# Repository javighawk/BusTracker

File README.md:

# BusTracker
Bus tracker in Raspberry Pi originally designed for Saskatoon transit. It will check the waiting time on desired stop(s) and display it on a 7-segment display.

Dependencies arre mantained through Ivy

The material used is:
- Raspberry Pi 3
- Adafruit 1.2" 7-segment red
- 2x Buttons

To run the program:
1. Place the GTFS static data on the folder "gtfs/" located on the base directory of the repository.
2. Run  Main.java. You will probably need to run it as superuser.

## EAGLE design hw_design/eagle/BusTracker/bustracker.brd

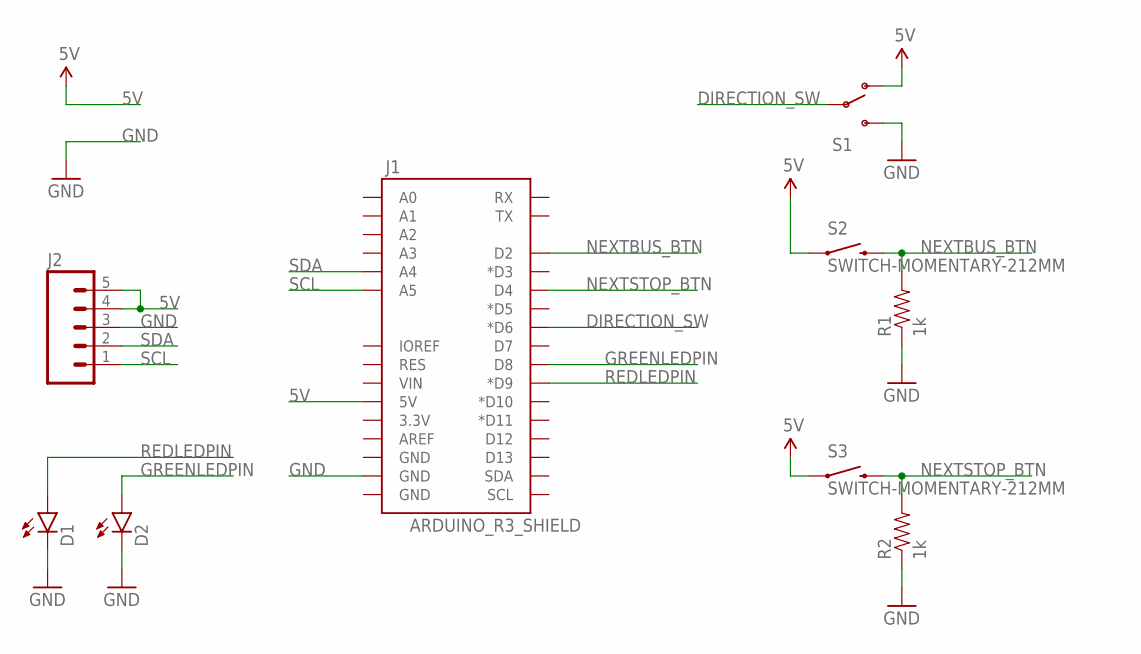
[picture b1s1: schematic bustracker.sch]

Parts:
D1, D2: LED5MM
J1: ARDUINO_R3_SHIELD; UNO_R3_SHIELD
J2: M05PTH; 1X05
R1, R2: 1k; AXIAL-0.3
S1: SWITCH-SPDTPTH; SWITCH-SPDT
S2, S3: SWITCH-MOMENTARY-212MM; TACTILE-PTH-12MM

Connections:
5V: J1.5V, J2.4, J2.5, S1.1 (O), S2.1, S3.1
DIRECTION_SW: J1.D6 (*D6), S1.2
GND: D1.K (C), D2.K (C), J1.GND@1 (GND), J2.3, R1.P$1 (1), R2.P$1 (1), S1.3 (S)
GREENLEDPIN: D2.A, J1.D8
NEXTBUS_BTN: J1.D2, R1.P$2 (2), S2.3 (2)
NEXTSTOP_BTN: J1.D4, R2.P$2 (2), S3.3 (2)
REDLEDPIN: D1.A, J1.D9 (*D9)
SCL: J1.A5, J2.1
SDA: J1.A4, J2.2

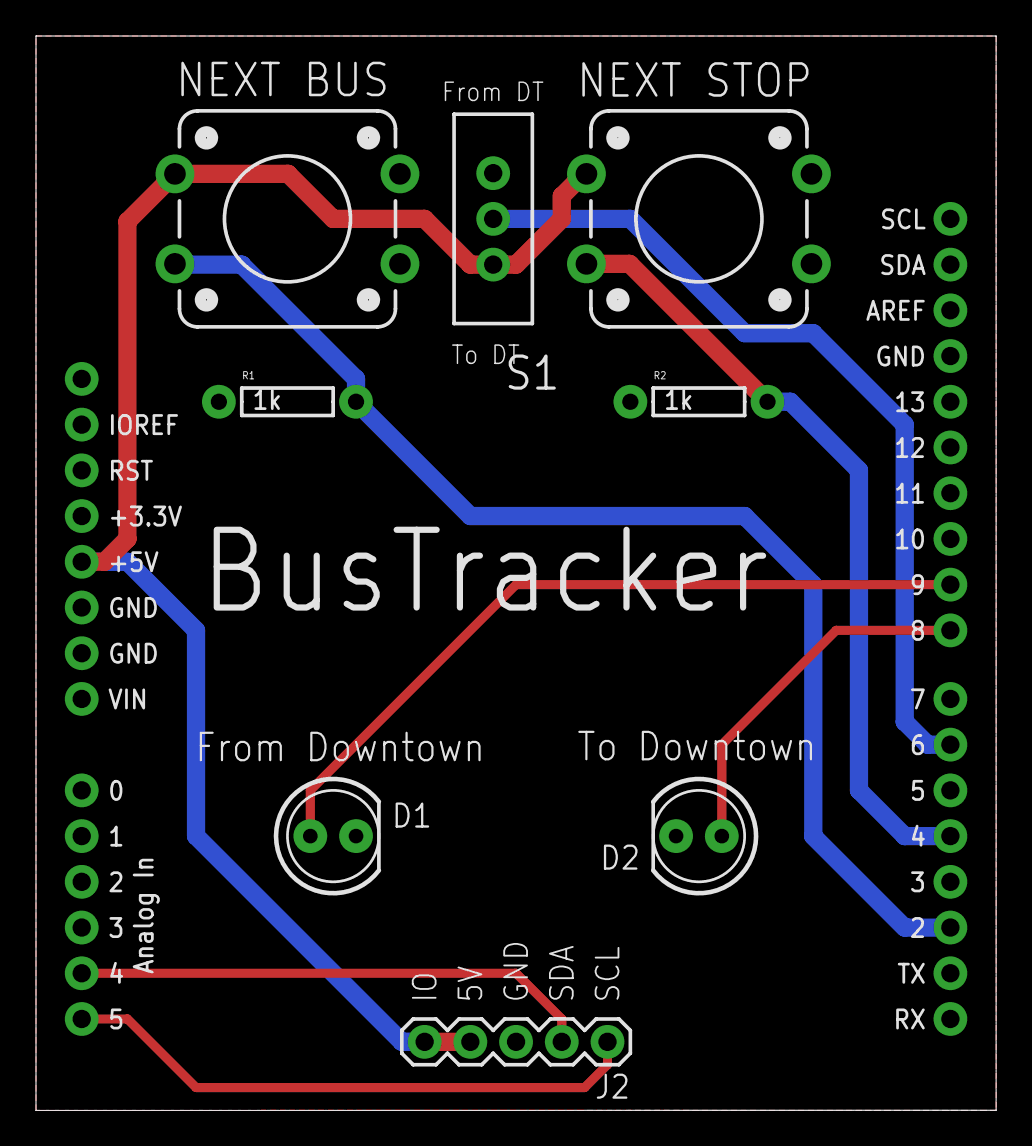
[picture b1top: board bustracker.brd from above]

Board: 2 copper layers, 53.3 x 59.7 mm, 9 parts (0 on the bottom side), 9 nets.

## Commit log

2016-01-27 :circus_tent: Added .gitattributes & .gitignore files
2016-01-27 Initial commit
    All files added
2016-01-31 Added waiting time calculation
    Added waiting time calculation.
    Erased the scheduled times from the program. They need to be taken from
    the GTFS feed and stored until they are outdated.
    Added 3 more bus stops but not being used at the moment
2016-02-05 Ported to Arduino
    All the program done in Eclipse has been ported to Arduino since the
    libraries to use the 7-segment display are for Arduino
2016-02-05 Added readme
2016-02-06 Added bus line parsing and error displaying
    Bus lines are now also parsed.
    Errors during the website download are displayed now in the 7-segment
    displayed
2016-02-12 Included lastTime variable
    Included a variable to show when was the last time the BusStop data was
    updated
2016-02-12 Fixed bus line display
    Fixed the displaying of the bus line. Now the bus line is always
    displayed either there is wait time information or not.
    Changed the error display format: Connection error will be shown now
    with a small dot over the waiting time and a not updated wait time will
    be signaled with the semicolon between the line and the wait time.
2016-02-12 Fixed connection problems handling
    Modified the way the connection problems are handled, so at no moment
    the program should get stuck, but notify the problem through the display
2016-02-12 Fixed a bug in time at noon & lastUpdated refresh
    Fixed a bug that appeared when it was 12PM, where the waiting time
    suddenly appeared to be 12 hours of wait.
    Added also a line to update the lastUpdated variable of the BusStop that
    we are parsing for.
2016-02-12 Added interrupts for GPIO and a function to retrieve all the info
    Added interrupts to handle two buttons to show different wait times and
    bus lines.
    Added a function that retrieves the informaton given a set of bus stops
2016-04-09 Added some comments
2016-07-23 Reviewed code for Arduino
2016-07-23 Added info to some comments
2016-07-23 Fixed indentation
2016-07-23 Modified comments and bus stop name. Added watchdog func
2016-07-23 Modified comments and removed unused functions
2016-07-23 Modif comments, added display funcs, removd unused vars
2016-07-23 Modified comments
2016-07-23 Revert "Finished Watchdog implementation"
2016-07-23 Added comments
2016-07-24 Removed interrupts due to malfunction
2016-07-24 Stored strings in defines
2016-07-24 Erased colon switch
2016-07-24 Added new bus line
2016-07-24 Changed analogRead for Interrupt. Added intrrpt unbouncing function
2016-07-24 Arranged letters and numbers BCD codes in #defines
2016-07-24 Added pseudo-interrupts for bus stop change and bus direction change (from/to downtown)
2016-07-24 Fixed bug in parsing
2016-07-24 Modified typo in doc
2016-07-24 Added doc to Parsing Manager
2016-08-01 Created PCB for BusTracker
2016-08-01 Added silkscreen layer
2016-08-01 Changed I2C pins position
2016-08-01 Added BusTracker label on silkscreen layer
2016-08-01 Added signature on the back
2016-08-06 Changed silkscreen font
2016-12-24 Added Java files
2016-12-24 Modified Git ignore
2016-12-24 Modified README
2016-12-24 Added GTFS parser
2016-12-24 Added function to query data from GTFS static data
2016-12-24 Added functions to run queries against the parsed data
2016-12-24 Reorganized main function
2016-12-24 Added lines
2016-12-24 Added comment
2016-12-24 Added print of scheduled time
2016-12-25 Added timezone extraction
2016-12-25 Finished code to calculate waiting time
2016-12-25 Erased line
2016-12-25 Reorganized code
2016-12-25 Reorganized code 2
2016-12-25 Deleted Vehicle class
2016-12-25 Erased traces, handle non-valid routes, handle direction change
2016-12-30 Many changes have been done. Still under development
2016-12-30 Documentation format
2016-12-30 Added new constructor
2016-12-30 Added service dates to wait times at initialization
2016-12-30 Erased unused constructors
2016-12-30 Added start/end dates
2016-12-30 Doc format
2016-12-30 Finished bus tracking
2016-12-30 Erased traces
2016-12-30 Avoid ignoring future delayed buses. Avoid 1min error wait
2016-12-30 Modified doc
2016-12-31 Force date change at 3AM
2017-01-02 Modified gitignore
2017-01-02 Added GTFS path as argument
2017-01-02 Handled no Internet connection
2017-01-02 Modified doc:
2017-01-02 Added Display class to control the 7-segment display
2017-01-03 Store upcoming buses into an array
2017-01-03 Add all BusStopTrackThread objects into an array
2017-01-04 Store all bus stop names into a String array
2017-01-04 Added functions to modify the display
2017-01-04 Changed location of variable
2017-01-04 Erased url String from BusStopTrackThread
2017-01-04 Changed location of method
2017-01-04 Added call from BusStopTrackThread to update bus data
2017-01-04 Modified code to write waiting time on display
2017-01-04 Added realtime indicator. Avoided use of display, print on screen waiting time
2017-01-20 Added connection to Display over I2C
2017-01-20 Added support to know if the bus waiting time is real time or not
2017-01-24 Fixed bugs and added auxiliary functions
2017-01-24 Added GPIO
2017-01-24 Changed method modifier to synchronized
2017-01-24 Added direction update on constructor
2017-01-24 Change order of operations at the end of init
2017-01-24 Trying to fix sigsegv error
2017-01-28 Fixed bug when displaying
2017-01-28 Fixed bugs
2017-03-12 Added Ivy file
2017-03-13 Added interfaces and reorganized project (under development)
2017-03-13 Added implementation of TripStop
2017-03-13 Added implementations (under development)
2017-04-02 Added implementation of GTFSManager
2017-04-02 Added busStopId field on TripStop class
2017-04-03 Changed organization of subjects and observables
2017-04-22 Fixed BusStop
2017-04-22 Fixed GTFS static data. Added needed methods
2017-04-22 Erased all exceptions thrown and placed Optionals instead
2017-04-23 Fixed GTFS Manager
2017-04-23 Added function to unsubscribe bus stops
2017-04-23 Removed old copy of BusStop implementation
2017-04-23 Include exception handling on GTFSManager constructor
2017-04-23 Pass GTFS static data path as argument and start parsing right away
2017-04-23 Leave buttons manager empty for the moment (Testing purposes)
2017-04-23 Modified main for an initial test
2017-04-25 Added slf4j
2017-04-25 Fixed errors and erased unused files
2017-04-28 Changed fields of TripStop to Optional
2017-04-28 Use String as scheduled arrival
2017-04-28 Fixed automatic refactoring
2017-04-28 Fixed null pointer exception
2017-04-28 Fixed: When more than one bus arrive at the same time, only one was shown
2017-04-29 Erased Optional attributes from TripStop
2017-04-29 Created TripStopUpdate and use it instead of TripStop when passing updates
2017-04-29 Fixed logging
2017-04-29 Added weekdays of operation to TripStop
2017-04-30 Fixed bug on calculation of Real time of arrival
2017-04-30 Added TripCalendar, in charge of determining if a trip is active or a given day or not
2017-04-30 Fixed bug on TripStopThreads
2017-04-30 Added service exception to TripCalendar and moved calendar-related classes to new package
2017-04-30 Erased redundant line on ivy file
2017-05-06 Fix arrival time and date for arrival hours higher than 23
2017-05-06 Moved files into 'main' folder
2017-05-06 Added test
2017-05-06 Fixed import style
2017-05-06 Added timeout task for the trip stop to change isRealTime to false
2017-05-06 Removed unused methods
2017-05-07 Moved display classes into display package
2017-05-07 Added task to update display
2017-05-07 Hooked up display to main
2017-05-07 Fixed import
2017-05-07 Added function to clear realtime indicator and to show the index of the upcoming bus
2017-05-14 Changed busStopId, busLine and tripId from String to integer
2017-05-14 Added display handling
2017-05-14 Erased old files
2017-05-14 Moved User Input Event into GPIOManager
2017-05-14 Finalize GPIO handling. Add create methods instead of subscribing and starting tasks on constructor
2017-05-14 Add createAndStart method instead of starting task on constructor
2017-05-14 Finalize dependency injection on Main
2017-05-14 Added bus stop to track on Main
2017-05-14 Changed git ignore
2017-05-14 Fixed bug after change from String to Integer on Stop Ids
2017-05-15 Added logging messages
2017-05-16 Created interfaces of GTFSManager and GTFSStaticData to mock them on tests
2017-05-16 Added test for BusStopManager. Added dependency on Mockito
2017-05-16 Sort BusStops by busStopId when calling getNextBusStop on BusStopManager
2017-05-16 Fixed test for BusStopManager
2017-05-17 Fixed bug on getNextBusStop function
2017-05-17 Added more test cases to BusStopManager test
2017-05-17 Update display when a new bus stop is added or removed
2017-05-17 Added test for BusStop
2017-05-17 Erased unused PublishSubject on BusStop
2017-05-17 Modified log on DisplayManager
2017-05-17 Fixed bug displaying the trip index
2017-05-28 Update readme again

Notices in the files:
parts and their libraries:
SparkFun-LED: Licensing: Creative Commons ShareAlike 4.0 International - https://creativecommons.org/licenses/by-sa/4.0
